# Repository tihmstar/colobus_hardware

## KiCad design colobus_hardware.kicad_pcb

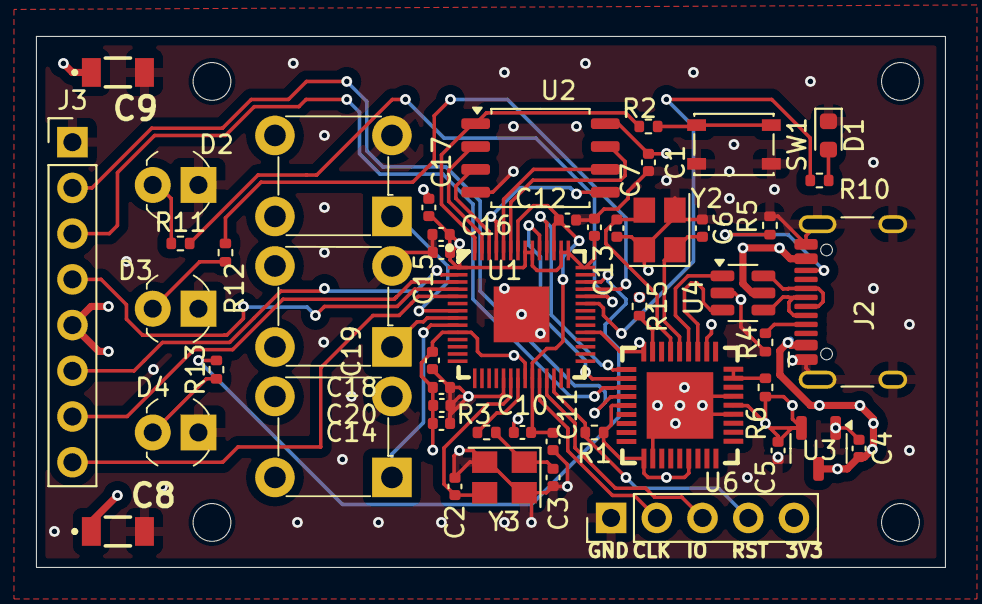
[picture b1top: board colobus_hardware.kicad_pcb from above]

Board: 4 copper layers, 50.5 x 29.5 mm, 53 parts (0 on the bottom side), 46 nets.

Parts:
Button1, Button2, Button3: PTH_12x12mm_h8.0mm; Switch_Tactile_THT_6x6mm
C1, C4, C5: 0.1uF; C_0402_1005Metric
C2, C3, C6, C7: 15pF; C_0402_1005Metric
C8, C9: 100uF; GRM31x
C10, C11, C14, C15, C16, C17, C18, C19, C20: 100n; C_0402_1005Metric
C12, C13: 1u; C_0402_1005Metric
D1: LED1; LED_0603_1608Metric
D2: LED2; LED_3mm_Radial
D3: LED3; LED_3mm_Radial
D4: LED4; LED_3mm_Radial
H1, H2, H3, H4: MountingHole; MountingHole_2.1mm
J1: SWD; PinHeader_1x05_P2.54mm_Vertical
J2: USB_C_Receptacle_USB2.0_16P; USB_C_Receptacle_HCTL_HC-TYPE-C-16P-01A
J3: Lightning; PinHeader_1x08_P2.54mm_Vertical
R1, R2, R3, R6: 1k; R_0402_1005Metric
R4, R5: 5.1k; R_0402_1005Metric
R10, R11, R12, R13: 470; R_0402_1005Metric
R15: 12k; R_0402_1005Metric
SW1: BOOTSEL; SW_SPST_PTS810
U1: RP2040; LQFN-56_L7.0-W7.0-P0.4-EP
U2: W25Q128JVS; SOIC-8_5.23x5.23mm_P1.27mm
U3: XC6206PxxxMR; SOT-23-3
U4: USBLC6-2SC6; SOT-23-6
U6: USB2512B/M2; UQFN-36_L6.0-W6.0-P0.50-BL-EP3.7
Y2: ABM8G-24.000MHZ-18-D2Y-T; Crystal_SMD_Abracon_ABM8G-4Pin_3.2x2.5mm
Y3: ABM8-272-T3; Crystal_SMD_Abracon_ABM8G-4Pin_3.2x2.5mm

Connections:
5V: C4.1, C8.1, C9.1, J2.A4 (VBUS), J2.A9 (VBUS), J2.B4 (VBUS), J2.B9 (VBUS), J3.5, U3.3 (VI), U4.5 (VBUS)
+1V1: C10.1, C11.1, C12.1, U1.23 (DVDD), U1.45 (VREG_VOUT), U1.50 (DVDD)
+3V3: C1.1, C5.1, C13.1, C14.1, C15.1, C16.1, C17.1, C18.1, C19.1, C20.1, J1.5, R1.1, R6.1, U1.1 (IOVDD), U1.10 (IOVDD), U1.22 (IOVDD), U1.33 (IOVDD), U1.42 (IOVDD), U1.43 (ADC_AVDD), U1.44 (VREG_IN), U1.48 (USB_VDD), U1.49 (IOVDD), U2.8 (VCC), U3.2 (VO), U6.5 (VDDA33), U6.10 (VDDA33), U6.15 (VDD33), U6.23 (VDD33), U6.29 (VDDA33), U6.36 (VDDA33)
BTN1: Button1.1, U1.7 (GPIO5)
BTN2: Button2.1, U1.8 (GPIO6)
BTN3: Button3.1, U1.9 (GPIO7)
D_N: U4.3 (I/O2), U6.30 (USBDM_UP)
D_P: U4.1 (I/O1), U6.31 (USBDP_UP)
GND: Button1.2, Button2.2, Button3.2, C1.2, C2.1, C3.1, C4.2, C5.2, C6.1, C7.1, C8.2, C9.2, C10.2, C11.2, C12.2, C13.2, C14.2, C15.2, C16.2, C17.2, C18.2, C19.2, C20.2, D1.1 (K), D2.1 (K), D3.1 (K), D4.1 (K), J1.1, J2.A1 (GND), J2.A12 (GND), J2.B1 (GND), J2.B12 (GND), J2.S1 (SHIELD), J3.1, R4.1, R5.1, R15.2, SW1.1, U1.19 (TESTEN), U1.57 (GND), U2.4 (GND), U3.1 (GND), U4.2 (GND), U6.11 (TEST), U6.22 (SDA/SMBDATA), U6.24 (SCL/SMBCLK/CFG_SEL0), U6.37 (EXP), Y2.2, Y2.4, Y3.2, Y3.4
ID0: J3.4, U1.4 (GPIO2)
ID1: J3.8, U1.5 (GPIO3)
L0n: J3.3, U6.3 (USBDM_DN2/PRT_DIS_M2)
L0p: J3.2, U6.4 (USBDP_DN2/PRT_DIS_P2)
L1n: J3.6, U1.2 (GPIO0)
L1p: J3.7, U1.3 (GPIO1)
LED1: R10.2, U1.37 (GPIO25)
LED2: R11.2, U1.38 (GPIO26_ADC0)
LED3: R12.2, U1.39 (GPIO27_ADC1)
LED4: R13.2, U1.40 (GPIO28_ADC2)
unnamed: C3.2, R3.2, Y3.1
unnamed: D1.2 (A), R10.1
unnamed: D2.2 (A), R11.1
unnamed: D3.2 (A), R12.1
unnamed: D4.2 (A), R13.1
unnamed: J2.A5 (CC1), R4.2
unnamed: J2.B5 (CC2), R5.2
unnamed: R2.1, SW1.2
unnamed: U1.52 (QSPI_SCLK), U2.6 (CLK)
unnamed: U1.53 (QSPI_SD0), U2.5 (DI(IO0))
unnamed: U1.55 (QSPI_SD1), U2.2 (DO(IO1))
unnamed: U1.54 (QSPI_SD2), U2.3 (IO2)
unnamed: U1.51 (QSPI_SD3), U2.7 (IO3)
unnamed: R2.2, U1.56 (QSPI_SS), U2.1 (~CS)
unnamed: C2.2, U1.20 (XIN), Y3.3
unnamed: R3.1, U1.21 (XOUT)
unnamed: R15.1, U6.35 (RBIAS)
unnamed: R6.2, U6.26 (RESET_N), U6.27 (VBUS_DET)
unnamed: C7.2, U6.33 (XTALIN/CLKIN), Y2.3
unnamed: C6.2, U6.32 (XTALOUT), Y2.1
PICO_D_N: U1.46 (USB_DM), U6.1 (USBDM_DN1/PRT_DIS_M1)
PICO_D_P: U1.47 (USB_DP), U6.2 (USBDP_DN1/PRT_DIS_P1)
SWDCLK: J1.2, U1.24 (SWCLK)
SWDIO: J1.3, U1.25 (SWD)
USB_DN: J2.A7 (D-), J2.B7 (D-), U4.4 (I/O2)
USB_DP: J2.A6 (D+), J2.B6 (D+), U4.6 (I/O1)
~RESET: J1.4, R1.2, U1.26 (RUN)

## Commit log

2025-06-11 public release
2025-06-11 add LICENSE
